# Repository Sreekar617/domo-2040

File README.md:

# domo-2040
A custom microcontroller built around the RP2040

## Features
* RP2040 microcontroller
* 27 GPIO pins
* 16MB flash memory
* Onboard user button (GPIO24)
* Onboard user LED (GPIO25)
* USB-C connection
* Compatible with Pi Pico footprint
* Super cool decoration
* Cute Domos
## Why?
I use devboards like the Pi Pico all the time, but I never really understood how they worked or anything. Specifically, I was curious as to why projects tend to use premade devboards such as Pi Picos rather than just use a plain RP2040. So naturally, I decided the best way to learn was to make one myself. Also, funnily enough the BOM comes out to about half the retail price of the Pico before countimg one-time assembly fees, which means if I were to theoretically mass produce this me and my friends could get devboards at about half price. 
## BOM
| Component        | Specification | Quantity | LCSC Part # | Price |
|------------------|---------------|----------|-------------|-------|
| Capacitor 0402   | 1uF           | 2        | C52923      | $0.02 |
| Capacitor 0402   | 0.1uF         | 11       | C1525       | $0.06 |
| Capacitor 0402   | 33pF          | 2        | C1562       | $0.02 |
| Capacitor 0603   | 10uF          | 2        | C19702      | $0.20 |
| Diode SOD-323    | Schottky      | 1        | C191023     | $0.02 |
| LED 0603         | White LED     | 1        | C2290       | $0.02 |
| USB C Receptacle | USB C         | 1        | C2765186    | $0.21 |
| Resistor 0402    | 5.1k          | 2        | C25905      | $0.01 |
| Resistor 0402    | 27            | 2        | C25156      | $0.02 |
| Resistor 0402    | 1k            | 3        | C11702      | $0.02 |
| Resistor 0402    | 10k           | 2        | C25744      | $0.01 |
| Switch           | Alps SKRK     | 2        | C720477     | $0.11 |
| MCU              | RP2040        | 1        | C2040       | $2.00 |
| Flash Chip       | 128Mbit       | 1        | C97521      | $2.65 |
| LDO SOT-23       | 5v->3v3       | 1        | C5446       | $0.20 |
| Crystal          | 12MHz         | 1        | C9002       | $0.20 |
| ~~**Soldering Iron**~~ | |             1        |   stole it from a friend lol          |~~$20~~ |

## Demos!
I don't have access to a breadboard or anything to control with the devboard at the moment (:heavysob:) but here's a [video](https://cdn.hackclub.com/01a0e574-c0dc-76d3-b759-e71435e16d3c/IMG_4351.mp4) of the User-Controlled LED lighting up, and another [video](https://user-cdn.hackclub-assets.com/01a15276-ad8b-79ea-be17-06658552e3f3/IMG_4345.MOV) of me attempting to use a macgeyvered button to control the user LED

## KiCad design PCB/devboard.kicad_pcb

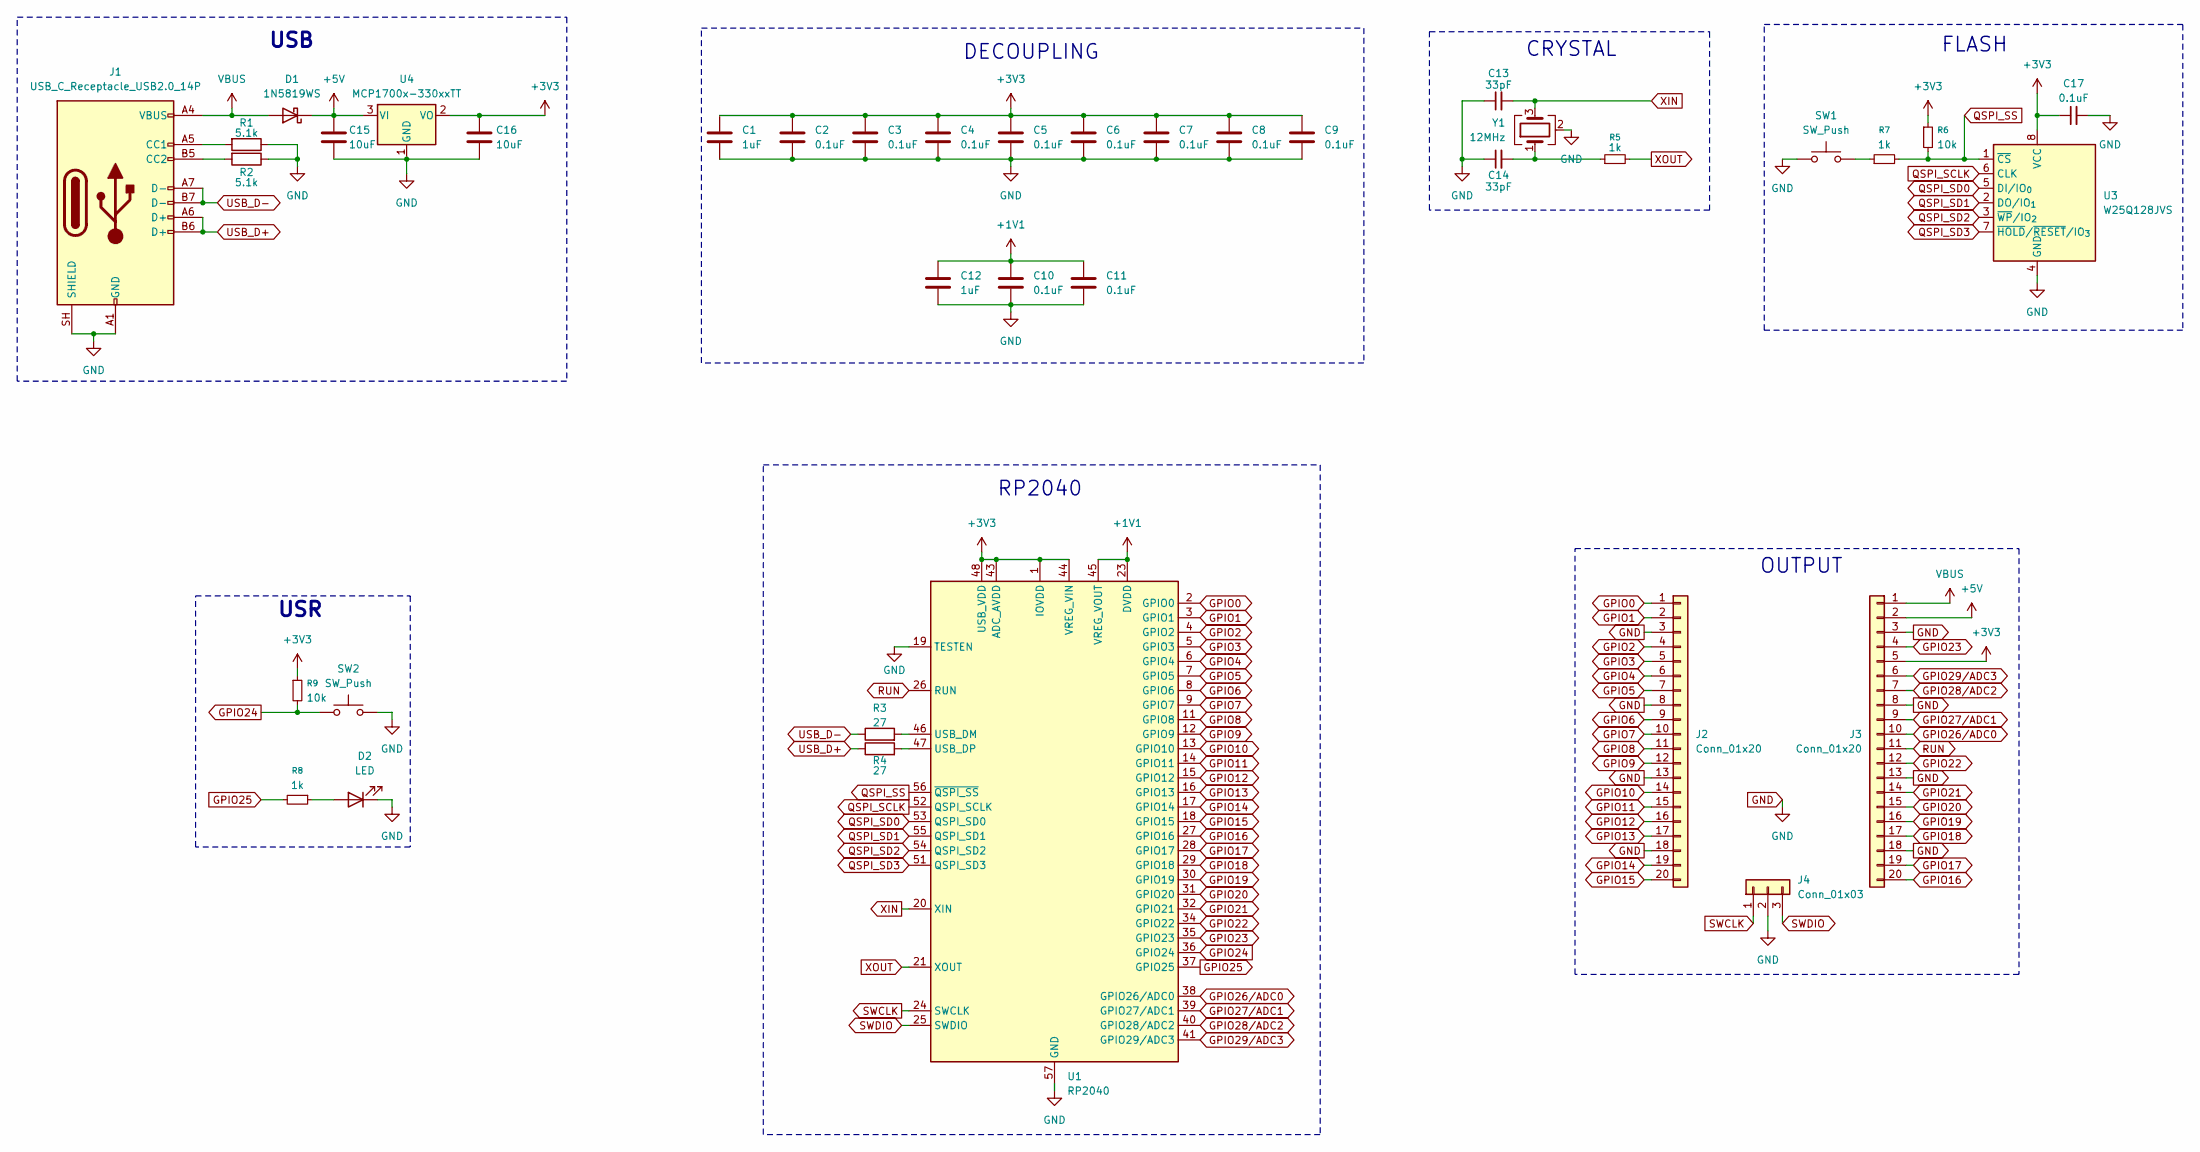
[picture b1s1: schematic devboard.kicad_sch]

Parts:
C1, C12: 1uF; C_0402_1005Metric; LCSC Part # C52923
C2, C3, C4, C5, C6, C7, C8, C9, C10, C11, C17: 0.1uF; C_0402_1005Metric; LCSC Part # C1525
C13, C14: 33pF; C_0402_1005Metric; LCSC Part # C1562
C15, C16: 10uF; C_0603_1608Metric; LCSC Part # C19702
D1: 1N5819WS; D_SOD-323; LCSC Part # C191023
D2: LED; LED_0603_1608Metric; LCSC Part # C2288
J1: USB_C_Receptacle_USB2.0_14P; USB_C_Receptacle_HRO_TYPE-C-31-M-12; LCSC Part # C2765186
J2, J3: Conn_01x20; PinHeader_1x20_P2.54mm_Vertical; LCSC Part # C50981
J4: Conn_01x03; PinHeader_1x03_P2.54mm_Vertical; LCSC Part # C24980
R1, R2: 5.1k; R_0402_1005Metric; LCSC Part # C25905
R3, R4: 27; R_0402_1005Metric; LCSC Part # C25100
R5, R7, R8: 1k; R_0402_1005Metric; LCSC Part # C11702
R6, R9: 10k; R_0402_1005Metric; LCSC Part # C25744
SW1, SW2: SW_Push; SW_Push_SPST_NO_Alps_SKRK; LCSC Part # C720477
U1: RP2040; QFN-56-1EP_7x7mm_P0.4mm_EP3.2x3.2mm; LCSC Part # CF2040
U3: W25Q128JVS; SOIC-8_5.3x5.3mm_P1.27mm; LCSC Part # C97521
U4: MCP1700x-330xxTT; SOT-23; LCSC Part # C5446
Y1: 12MHz; Crystal_SMD_3225-4Pin_3.2x2.5mm; LCSC Part # C9002

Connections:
+1V1: C10.1, C11.1, C12.1, U1.23 (DVDD), U1.45 (VREG_VOUT), U1.50 (DVDD)
+3V3: C1.1, C2.1, C3.1, C4.1, C5.1, C6.1, C7.1, C8.1, C9.1, C16.1, C17.1, J3.5, R6.1, R9.1, U1.1 (IOVDD), U1.10 (IOVDD), U1.22 (IOVDD), U1.33 (IOVDD), U1.42 (IOVDD), U1.43 (ADC_AVDD), U1.44 (VREG_VIN), U1.48 (USB_VDD), U1.49 (IOVDD), U3.8 (VCC), U4.2 (VO)
+5V: C15.1, D1.1 (K), J3.2, U4.3 (VI)
GND: C1.2, C2.2, C3.2, C4.2, C5.2, C6.2, C7.2, C8.2, C9.2, C10.2, C11.2, C12.2, C13.1, C14.1, C15.2, C16.2, C17.2, D2.1 (K), J1.A1 (GND), J1.A12 (GND), J1.B1 (GND), J1.B12 (GND), J1.SH (SHIELD), J2.3, J2.8, J2.13, J2.18, J3.3, J3.8, J3.13, J3.18, J4.2, R1.1, R2.1, SW1.1, SW2.2, U1.19 (TESTEN), U1.57 (GND), U3.4 (GND), U4.1 (GND), Y1.2 (G), Y1.4 (G)
GPIO0: J2.1, U1.2 (GPIO0)
GPIO1: J2.2, U1.3 (GPIO1)
GPIO2: J2.4, U1.4 (GPIO2)
GPIO3: J2.5, U1.5 (GPIO3)
GPIO4: J2.6, U1.6 (GPIO4)
GPIO5: J2.7, U1.7 (GPIO5)
GPIO6: J2.9, U1.8 (GPIO6)
GPIO7: J2.10, U1.9 (GPIO7)
GPIO8: J2.11, U1.11 (GPIO8)
GPIO9: J2.12, U1.12 (GPIO9)
GPIO10: J2.14, U1.13 (GPIO10)
GPIO11: J2.15, U1.14 (GPIO11)
GPIO12: J2.16, U1.15 (GPIO12)
GPIO13: J2.17, U1.16 (GPIO13)
GPIO14: J2.19, U1.17 (GPIO14)
GPIO15: J2.20, U1.18 (GPIO15)
GPIO16: J3.20, U1.27 (GPIO16)
GPIO17: J3.19, U1.28 (GPIO17)
GPIO18: J3.17, U1.29 (GPIO18)
GPIO19: J3.16, U1.30 (GPIO19)
GPIO20: J3.15, U1.31 (GPIO20)
GPIO21: J3.14, U1.32 (GPIO21)
GPIO22: J3.12, U1.34 (GPIO22)
GPIO23: J3.4, U1.35 (GPIO23)
GPIO24: R9.2, SW2.1, U1.36 (GPIO24)
GPIO25: R8.2, U1.37 (GPIO25)
GPIO26/ADC0: J3.10, U1.38 (GPIO26/ADC0)
GPIO27/ADC1: J3.9, U1.39 (GPIO27/ADC1)
GPIO28/ADC2: J3.7, U1.40 (GPIO28/ADC2)
GPIO29/ADC3: J3.6, U1.41 (GPIO29/ADC3)
unnamed: C14.2, R5.1, Y1.1
unnamed: D2.2 (A), R8.1
unnamed: J1.A5 (CC1), R1.2
unnamed: J1.B5 (CC2), R2.2
unnamed: R7.1, SW1.2
unnamed: R3.2, U1.46 (USB_DM)
unnamed: R4.2, U1.47 (USB_DP)
QSPI_SCLK: U1.52 (QSPI_SCLK), U3.6 (CLK)
QSPI_SD0: U1.53 (QSPI_SD0), U3.5 (DI/IO_{0})
QSPI_SD1: U1.55 (QSPI_SD1), U3.2 (DO/IO_{1})
QSPI_SD2: U1.54 (QSPI_SD2), U3.3 (~WP/IO_{2})
QSPI_SD3: U1.51 (QSPI_SD3), U3.7 (~HOLD/~RESET/IO_{3})
QSPI_SS: R6.2, R7.2, U1.56 (~QSPI_SS), U3.1 (~CS)
RUN: J3.11, U1.26 (RUN)
SWCLK: J4.1, U1.24 (SWCLK)
SWDIO: J4.3, U1.25 (SWDIO)
USB_D+: J1.A6 (D+), J1.B6 (D+), R4.1
USB_D-: J1.A7 (D-), J1.B7 (D-), R3.1
VBUS: D1.2 (A), J1.A4 (VBUS), J1.A9 (VBUS), J1.B4 (VBUS), J1.B9 (VBUS), J3.1
XIN: C13.2, U1.20 (XIN), Y1.3
XOUT: R5.2, U1.21 (XOUT)

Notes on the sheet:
USB
DECOUPLING
RP2040
FLASH
CRYSTAL
OUTPUT
USR

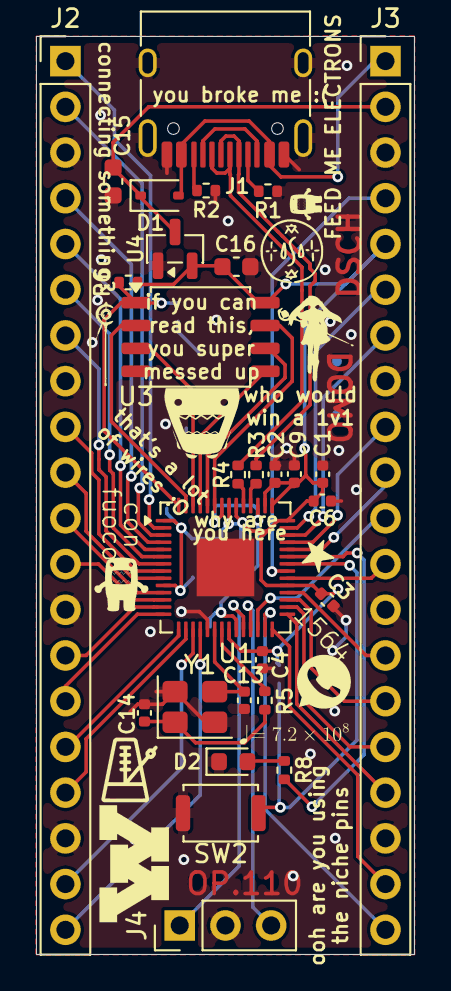
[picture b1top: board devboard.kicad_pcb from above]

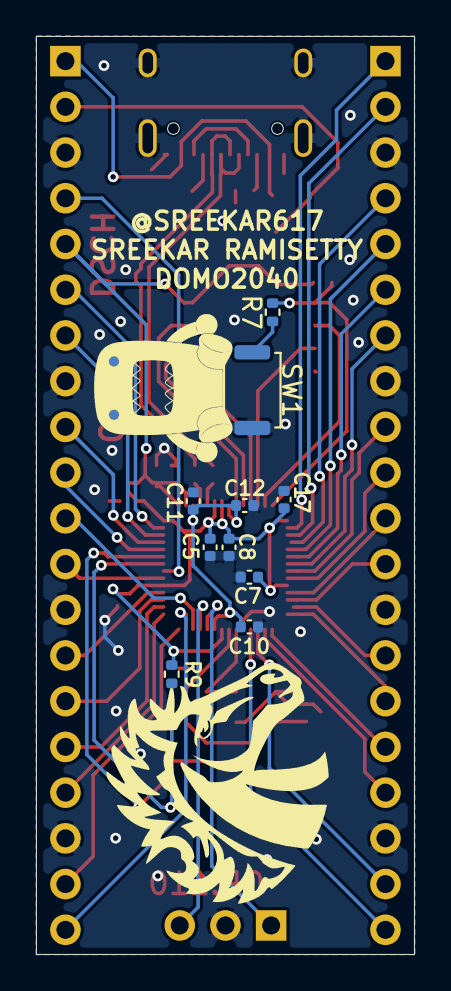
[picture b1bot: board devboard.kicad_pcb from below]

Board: 2 copper layers, 21.0 x 51.0 mm, 38 parts (10 on the bottom side), 55 nets.

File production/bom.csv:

"Reference","Qty","Value","DNP","Exclude from BOM","Exclude from Board","Footprint","Datasheet"
"C1,C12","2","1uF","","","","Capacitor_SMD:C_0402_1005Metric",""
"C2,C3,C4,C5,C6,C7,C8,C9,C10,C11,C17","11","0.1uF","","","","Capacitor_SMD:C_0402_1005Metric",""
"C13,C14","2","33pF","","","","Capacitor_SMD:C_0402_1005Metric",""
"C15,C16","2","10uF","","","","Capacitor_SMD:C_0603_1608Metric",""
"D1","1","1N5819WS","","","","Diode_SMD:D_SOD-323",""
"D2","1","LED","","","","LED_SMD:LED_0603_1608Metric",""
"J1","1","USB_C_Receptacle_USB2.0_14P","","","","Connector_USB:USB_C_Receptacle_HRO_TYPE-C-31-M-12","https://www.usb.org/sites/default/files/documents/usb_type-c.zip"
"J2,J3","2","Conn_01x20","","","","Connector_PinHeader_2.54mm:PinHeader_1x20_P2.54mm_Vertical",""
"J4","1","Conn_01x03","","","","Connector_PinHeader_2.54mm:PinHeader_1x03_P2.54mm_Vertical",""
"R1,R2","2","5.1k","","","","Resistor_SMD:R_0402_1005Metric",""
"R3,R4","2","27","","","","Resistor_SMD:R_0402_1005Metric",""
"R5,R7,R8","3","1k","","","","Resistor_SMD:R_0402_1005Metric",""
"R6,R9","2","10k","","","","Resistor_SMD:R_0402_1005Metric",""
"SW1,SW2","2","SW_Push","","","","Button_Switch_SMD:SW_Push_SPST_NO_Alps_SKRK",""
"U1","1","RP2040","","","","Package_DFN_QFN:QFN-56-1EP_7x7mm_P0.4mm_EP3.2x3.2mm","https://datasheets.raspberrypi.com/rp2040/rp2040-datasheet.pdf"
"U3","1","W25Q128JVS","","","","Package_SO:SOIC-8_5.3x5.3mm_P1.27mm","https://www.winbond.com/resource-files/w25q128jv_dtr%20revc%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"
"U4","1","MCP1700x-330xxTT","","","","Package_TO_SOT_SMD:SOT-23","http://ww1.microchip.com/downloads/en/DeviceDoc/20001826D.pdf"
"Y1","1","12MHz","","","","Crystal:Crystal_SMD_3225-4Pin_3.2x2.5mm",""

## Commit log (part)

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2026-06-29 add journal
2026-06-29 add gerbers
2026-06-29 add bom
2026-06-29 add pcb design files
2026-06-29 update production files
2026-06-29 reformat production files for JLC
